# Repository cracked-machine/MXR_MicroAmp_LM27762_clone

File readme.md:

## LM27762 Eval Board with OPAMP test circuit.

This is an eval board for the Texas Instruments [LM27762](hw/datasheets/lm27762.pdf) charge pump IC. It provides a +/-5V regulated split rail from +5.5V input.

To view the schematic click [here](hw/mxr_microamp.pdf).

A render of the board layout is below: 

### OpAmp test circuit

The board comes with an additional OpAmp test circuit based on the popular [MXR MicroAmp](https://www.electrosmash.com/mxr-microamp) "boost" guitar pedal. 

The circuit will accept a +9V power input, so this board can be used as a fully functional MicroAmp clone pedal. 

A reverse audio taper 500K pot should be attached to the `gain` header. If reverse audio cannot be obtained then biasing the potentiometer is possible. See schematic for details.

Wiring for the bypass switch should be done [off-board using a 3PDT switch](https://madbeanpedals.com/tutorials/downloads/MBP_FootswitchWiring.pdf).

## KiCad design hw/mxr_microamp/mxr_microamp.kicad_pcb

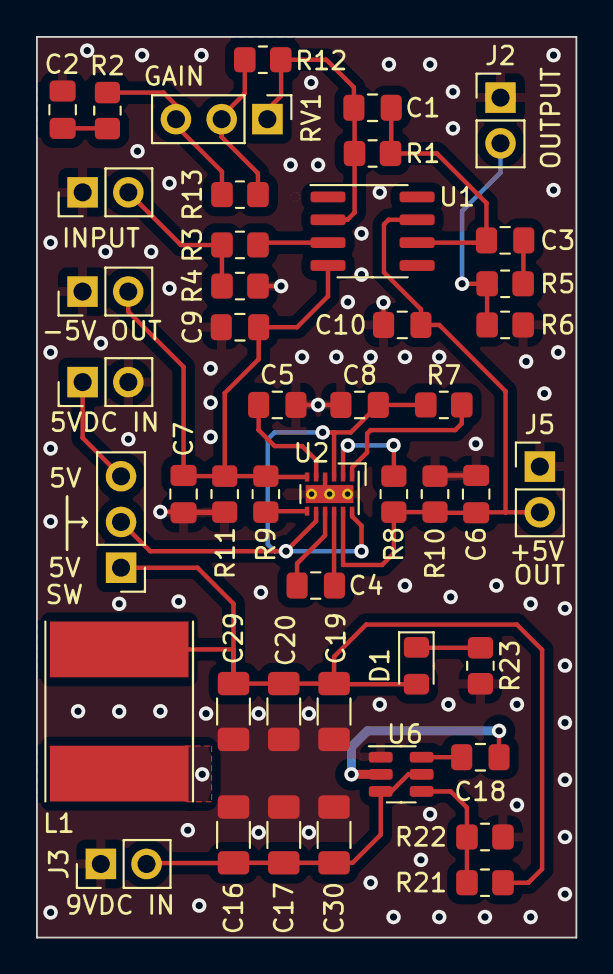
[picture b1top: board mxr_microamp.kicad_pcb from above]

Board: 2 copper layers, 30.0 x 50.0 mm, 46 parts (0 on the bottom side), 26 nets.

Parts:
C1: 47p; C_0805_2012Metric_Pad1.18x1.45mm_HandSolder
C2, C8: 4.7u; C_0805_2012Metric_Pad1.18x1.45mm_HandSolder
C3: 15u; C_0805_2012Metric_Pad1.18x1.45mm_HandSolder
C4: 1u; C_0805_2012Metric_Pad1.18x1.45mm_HandSolder
C5: 10u; C_0805_2012Metric_Pad1.18x1.45mm_HandSolder
C6, C7: 2.2u; C_0805_2012Metric_Pad1.18x1.45mm_HandSolder
C9, C10: 100n; C_0805_2012Metric_Pad1.18x1.45mm_HandSolder
C16, C17: 10uF; R_1206_3216Metric_Pad1.30x1.75mm_HandSolder
C18: 100nF; C_0805_2012Metric_Pad1.18x1.45mm_HandSolder
C19, C20, C29: 22uF; R_1206_3216Metric_Pad1.30x1.75mm_HandSolder
C30: 100nF; R_1206_3216Metric_Pad1.30x1.75mm_HandSolder
D1: RED; LED_0805_2012Metric_Pad1.15x1.40mm_HandSolder
J1: INPUT; PinHeader_1x02_P2.54mm_Vertical
J2: OUTPUT; PinHeader_1x02_P2.54mm_Vertical
J3: 9V IN; PinHeader_1x02_P2.54mm_Vertical
J4: -5V; PinHeader_1x02_P2.54mm_Vertical
J5: +5V; PinHeader_1x02_P2.54mm_Vertical
J6: POWER SELECT; PinHeader_1x03_P2.54mm_Vertical
J7: 5V IN; PinHeader_1x02_P2.54mm_Vertical
L1: 4.7uH; L_Taiyo-Yuden_NR-80xx_HandSoldering
R1, R4, R21: 56K; R_0805_2012Metric_Pad1.20x1.40mm_HandSolder
R2: 2.7K; R_0805_2012Metric_Pad1.20x1.40mm_HandSolder
R3: 1K; R_0805_2012Metric_Pad1.20x1.40mm_HandSolder
R5, R8, R9: 470R; R_0805_2012Metric_Pad1.20x1.40mm_HandSolder
R6, R7, R22: 10K; R_0805_2012Metric_Pad1.20x1.40mm_HandSolder
R10: 150; R_0805_2012Metric_Pad1.20x1.40mm_HandSolder
R11: 150R; R_0805_2012Metric_Pad1.20x1.40mm_HandSolder
R12: 100K; R_0805_2012Metric_Pad1.20x1.40mm_HandSolder
R13: 0R; R_0805_2012Metric_Pad1.20x1.40mm_HandSolder
R23: 2K2; R_0805_2012Metric_Pad1.20x1.40mm_HandSolder
RV1: 500K; PinHeader_1x03_P2.54mm_Vertical
U1: TL071; SOIC-8_3.9x4.9mm_P1.27mm
U2: LM27762; WSON-12-1EP_3x2mm_P0.5mm_EP1x2.65_ThermalVias
U6: TPS563200; SOT-23-6

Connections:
+5V: C6.1, C10.2, J5.2, R8.2, R10.1, U1.7 (V+), U2.11 (OUT+)
-5V: C7.1, C9.2, J4.2, R9.2, R11.1, U1.4 (V-), U2.6 (OUT-)
/buck/BUCK_VIN: C16.1, C17.1, C30.1, J3.2, U6.3 (VIN), U6.5 (EN)
/buck/BUCK_VOUT: C19.1, C20.1, C29.1, D1.2 (A), J6.1, L1.2, R21.1
/chargepump/CP_VIN: C8.1, J6.2, R7.1, U2.3 (VIN), U2.8 (EN-), U2.12 (EN+)
GND: C2.1, C5.2, C6.2, C7.2, C8.2, C9.1, C10.1, C16.2, C17.2, C19.2, C20.2, C29.2, C30.2, J1.1, J2.1, J3.1, J4.1, J5.1, J7.2, R4.1, R6.1, R10.2, R11.2, R22.2, R23.2, U2.4 (GND), U2.13 (PAD), U6.1 (GND)
unnamed: C1.2, C3.1, R1.2, U1.6
unnamed: C2.2, R2.1
unnamed: C3.2, R5.1
unnamed: D1.1 (K), R23.1
unnamed: J1.2, R3.1, R4.2
unnamed: J2.2, R5.2, R6.2
unnamed: J6.3, J7.1
unnamed: R12.1, R13.2, RV1.2
unnamed: R2.2, R13.1, RV1.3
unnamed: R3.2, U1.3 (+)
unnamed: C1.1, R1.1, R12.2, RV1.1, U1.2 (-)
unnamed: C4.2, U2.10 (C+)
unnamed: C4.1, U2.9 (C-)
unnamed: C5.1, U2.5 (CP)
unnamed: R8.1, U2.2 (FB+)
unnamed: R9.1, U2.7 (FB-)
unnamed: R7.2, U2.1 (PGOOD)
unnamed: C18.2, L1.1, U6.2 (SW)
unnamed: C18.1, U6.6 (VBST)
unnamed: R21.2, R22.1, U6.4 (VFB)

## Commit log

2023-04-19 added RevA
2023-04-19 added readme
